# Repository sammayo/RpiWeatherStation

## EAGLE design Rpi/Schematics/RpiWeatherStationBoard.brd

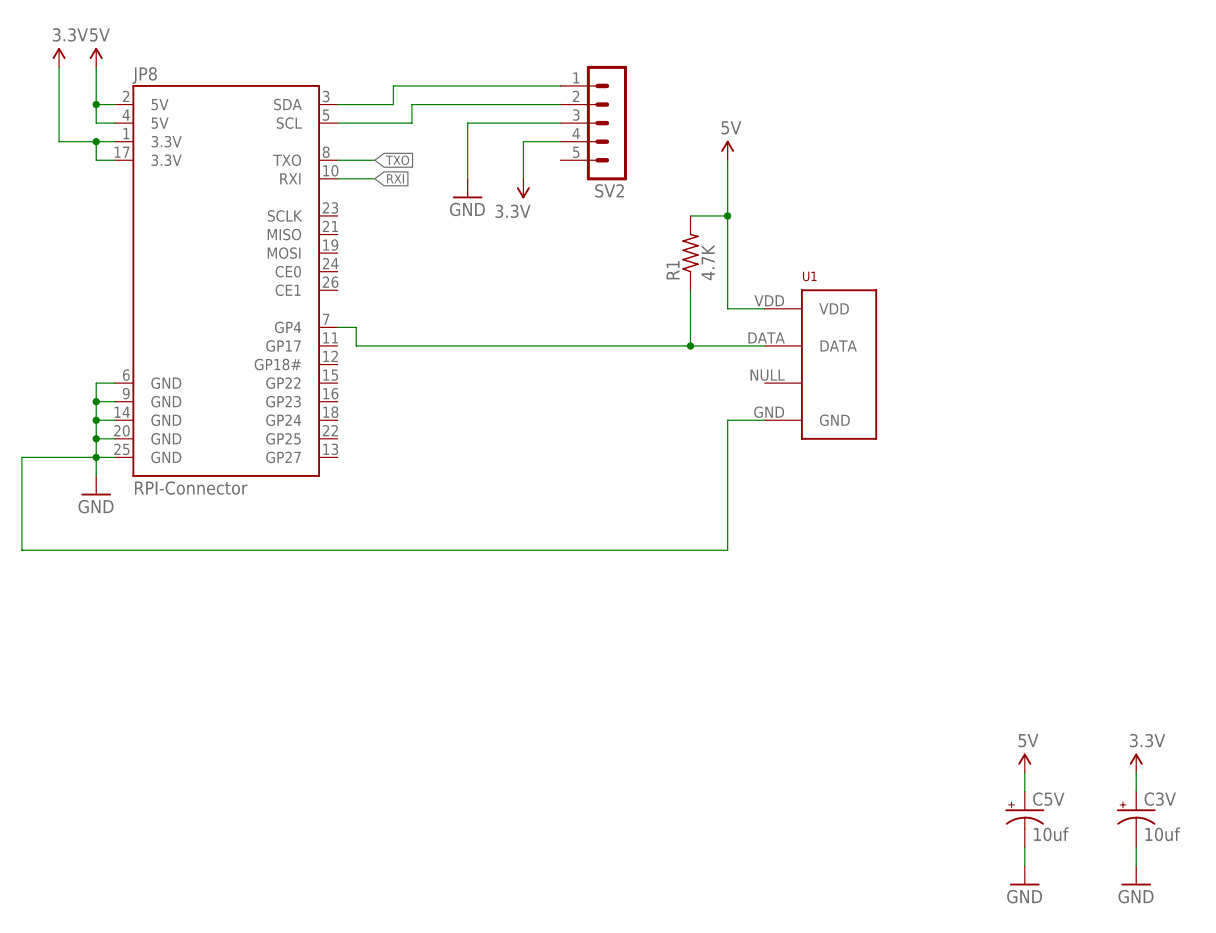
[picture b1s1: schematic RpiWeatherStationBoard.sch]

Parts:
C3V, C5V: 10uf; CPOL-RADIAL-10UF-25V-KIT
JP8: RPI-Connector; 2X13-SHROUDED
R1: 4.7K; 0207/10
SV2: MA05-1
U1: RHT03_DHT-22_AM2302WIRED; AM2302

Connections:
3.3V: C3V.1 (+), JP8.1 (3.3V), JP8.17 (3.3V), SV2.4
5V: C5V.1 (+), JP8.2 (5V), JP8.4 (5V), R1.2, U1.VDD
GND: C3V.2 (-), C5V.2 (-), JP8.6 (GND), JP8.9 (GND), JP8.14 (GND), JP8.20 (GND), JP8.25 (GND), SV2.3, U1.GND
unnamed: JP8.3 (SDA), SV2.1
unnamed: JP8.7 (GP4), R1.1, U1.DATA
unnamed: JP8.5 (SCL), SV2.2
RXI: JP8.10 (RXI)
TXO: JP8.8 (TXO)

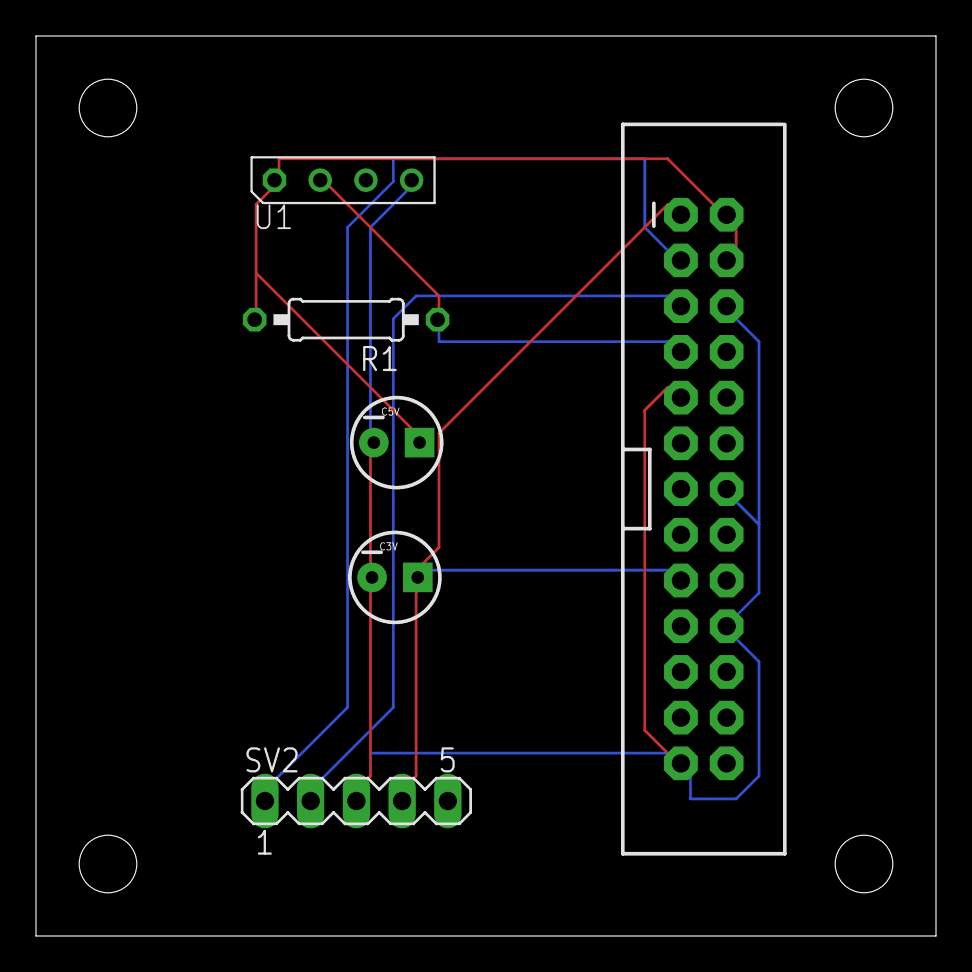
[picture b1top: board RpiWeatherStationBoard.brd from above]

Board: 2 copper layers, 50.0 x 50.0 mm, 6 parts (0 on the bottom side), 6 nets.

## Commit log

2015-01-23 adding .gitignore
2015-01-23 installed Yii
2015-02-07 moved composer file to directory 'WeatherStation'
2015-02-13 composer.lock
2015-02-13 created TestController and test view
2015-02-14 added dataLog and DataController
2015-02-14 moved dataLog to 'Server' directory
2015-02-14 configured 'urlManager' application component
2015-02-27 created SensorReader.py
2015-02-27 finished temperature and humidity readout sending to server
2015-02-28 created 'config-example.py' and added support for barometer
2015-03-02 added jqplot support
2015-03-03 Finished the basis of data plot displaying.
2015-03-06 Removed unnecessary first preamble line.
2015-03-06 removed arguments from checkArgs() to config.py
2015-03-06 renamed barometer config parameter
2015-03-06 cleaned up DataController.php and changes to config-example.py
2015-03-06 resolved conflict
2015-03-24 Added saving dynamic data to dynamicDataLog and static data to staticDataLog
2015-04-24 finished raspberry pi sensor readout code and added static data to plot page
2015-05-01 Fixed the issue with not working pretty URLs and turned savestatic to a POST request
2015-05-01 Added .htaccess to the web directory
2015-05-01 made post work for sendstatic and senddynamic on raspberry pi
2015-05-01 removed yii sample files and setup redirect from / to /show
2015-05-01 started downloading component schmatics into Schematics folder
2015-05-02 added temp/humidity and barometer schematics
2015-05-08 created schematic and board
2015-05-13 created gerber files for pcb
2015-05-13 .DS_Store removed
2015-05-15 resized board made it 2 layers
2015-05-29 deleted redundant gerber files and uploaded images and enclosure autocad drawing
2015-05-29 styled data page and added background

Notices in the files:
parts and their libraries:
SparkFun-Boards: Licensing: CC v3.0 Share-Alike You are welcome to use this library for commercial purposes.
